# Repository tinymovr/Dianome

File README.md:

# Dianome
Schematic and Board file for the Dianome R2 PDB

[OSHW] GR000006 | Certified open source hardware | oshwa.org/cert

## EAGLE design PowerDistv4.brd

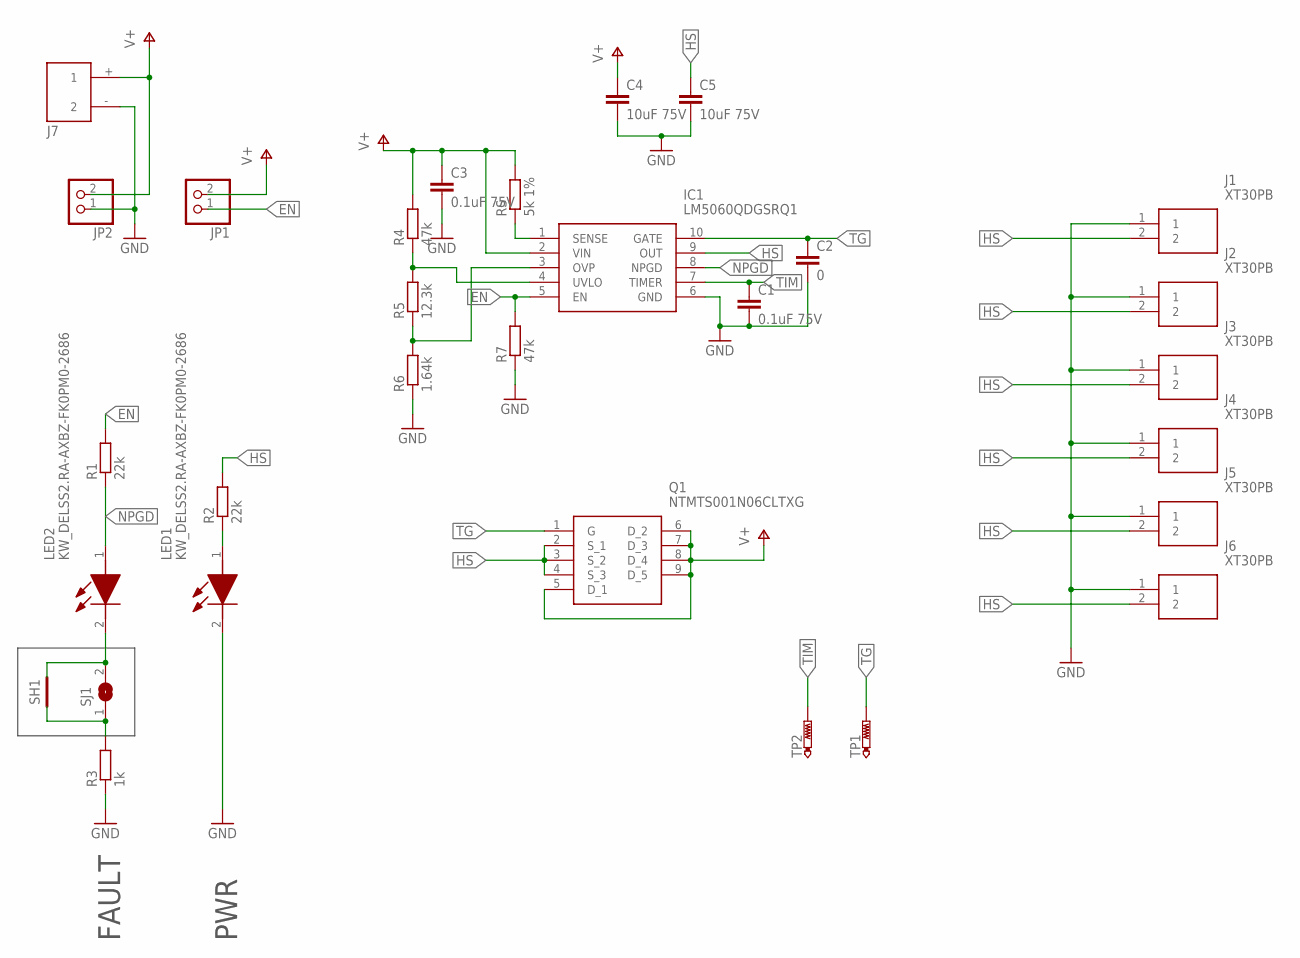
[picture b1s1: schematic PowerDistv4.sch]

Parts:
C1, C3: 0.1uF 75V; C0603K
C2: 0; C0603K
C4, C5: 10uF 75V; C1210
IC1: LM5060QDGSRQ1; SOP50P490X110-10N
J1, J2, J3, J4, J5, J6: XT30PB
J7: XT60_FEMALE
JP1, JP2: PINHD-1X02_2.54-S; 1X02-S
LED1, LED2: KW_DELSS2.RA-AXBZ-FK0PM0-2686; KWDELSS2RAAXBZFK0PM02686
Q1: NTMTS001N06CLTXG
R1, R2: 22k; R0603
R3: 1k; R0603
R4, R7: 47k; R0603
R5: 12.3k; R0603
R6: 1.64k; R0603
RS: 5k 1%; R0603
SH1: SHORTT5; SHORT_TOP-50
SJ1: SJ
TP1, TP2: PTR1PAD1-13; P1-13

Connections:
EN: IC1.5 (EN), JP1.1, R1.2, R7.2
GND: C1.2, C2.2, C3.2, C4.2, C5.2, IC1.6 (GND), J1.1, J2.1, J3.1, J4.1, J5.1, J6.1, J7.- (2), JP2.1, LED1.2 (K), R3.1, R6.1, R7.1
HS: C5.1, IC1.9 (OUT), J1.2, J2.2, J3.2, J4.2, J5.2, J6.2, Q1.2 (S_1), Q1.3 (S_2), Q1.4 (S_3), R2.2
unnamed: LED1.1 (A), R2.1
unnamed: IC1.1 (SENSE), RS.1
unnamed: IC1.3 (OVP), R5.1, R6.2
unnamed: LED2.2 (K), SH1.2, SJ1.2
unnamed: IC1.4 (UVLO), R4.1, R5.2
unnamed: R3.2, SH1.1, SJ1.1
NPGD: IC1.8 (NPGD), LED2.1 (A), R1.1
TG: C2.1, IC1.10 (GATE), Q1.1 (G), TP1.1
TIM: C1.1, IC1.7 (TIMER), TP2.1
V+: C3.1, C4.1, IC1.2 (VIN), J7.+ (1), JP1.2, JP2.2, Q1.5 (D_1), Q1.6 (D_2), Q1.7 (D_3), Q1.8 (D_4), Q1.9 (D_5), R4.2, RS.2

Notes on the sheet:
FAULT
PWR

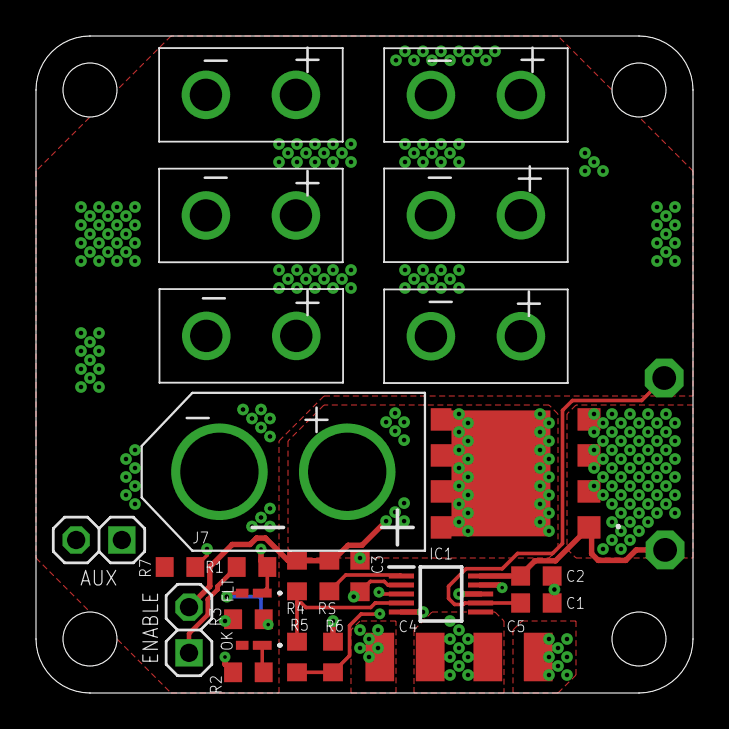
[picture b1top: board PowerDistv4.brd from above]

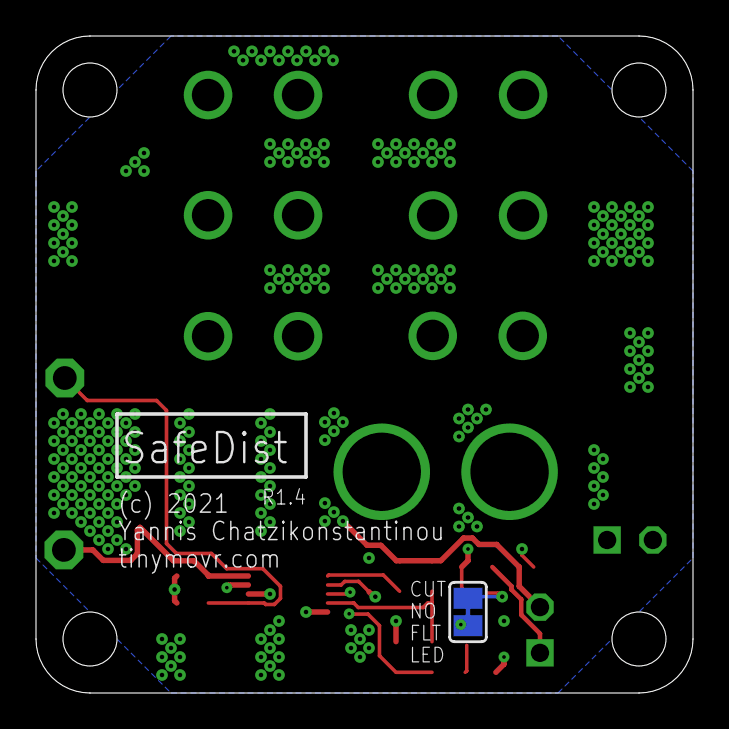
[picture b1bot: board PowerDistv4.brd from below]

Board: 4 copper layers, 36.5 x 36.5 mm, 30 parts (2 on the bottom side), 13 nets.

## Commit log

2021-08-30 Add board and schematic
2021-09-01 Rename PowerDistv4.brd to Dianome.brd
2021-09-01 Rename PowerDistv4.sch to Dianome.sch
2021-09-11 add docs
2021-09-11 update gitignore
2022-12-20 update project files
2022-12-20 minor layout changes
2022-12-20 add PDF
2022-12-20 Update LICENSE
2022-12-20 Create LICENSE
2022-12-20 Create COPYRIGHT
2022-12-22 Add OSHW certification info
2024-02-22 Add STEP file
